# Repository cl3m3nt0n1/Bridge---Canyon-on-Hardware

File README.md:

# Bridge---Canyon-on-Hardware
Welcome to Bridge, the hardware adaptation of Canyon, a convolution reverb plugin. This project utilizes ELK Audio OS and the Raspberry Pi Compute Module 4, featuring three custom-designed boards (1 main board and 2 IO boards). We created this project as the foundation for a complete OpenSource Audio FX Pedal based on community's resources. 

## Overview
Bridge extends Canyon's convolution reverb into the physical realm, combining the power of ELK Audio OS/HifiBerry DAC+ADC and Raspberry Pi Compute Module 4 for a robust audio FX solution.

## Features
- **Convolution Reverb:** Achieve realistic and immersive reverb effects through Canyon.
- **Custom Hardware:** Three boards - 1 main and 2 IO boards - designed for modularity and reusability.
- **ELK Audio OS:** Leverage the efficiency of ELK Audio OS for real-time audio processing.

## Hardware
Bridge comprises the following custom-designed boards:

1. **Main Board:**
   - GPIO/HAT Connector
   - SPI Screen Connector for a [480*320 ILI9488 based screen]([url](https://www.amazon.fr/gp/product/B08NV6SNYH/ref=ppx_yo_dt_b_asin_title_o00_s00?ie=UTF8&psc=1))
   - Raspberry Pi Compute Module 4
   - ATMega328p with ICSP connector for IO management

2. **IO Boards (x2):**
   - Pots and Switches for massive fun
   - Rotary encoder

## Software
Bridge relies on serveral pieces of sotware to run :
1. **ATMega328p:**
  - Potentiometer values conversion
  - Screen management
  - Serial communication with CM4
2. **Compute Module 4:**
  - Running ELK Audio OS for real-time audio processing
  - IO management
  - OSC
  - Serial Communication with ATMega328p

## Contributing
We welcome and encourage contributions to enhance Bridge! If you have ideas, bug fixes, or new features, please open an issue or submit a pull request.

## License
The software contained in this project is licensed under the GPL3 license. The hardware is licensed under the Creative Commons v4.0.

Happy coding with Bridge!

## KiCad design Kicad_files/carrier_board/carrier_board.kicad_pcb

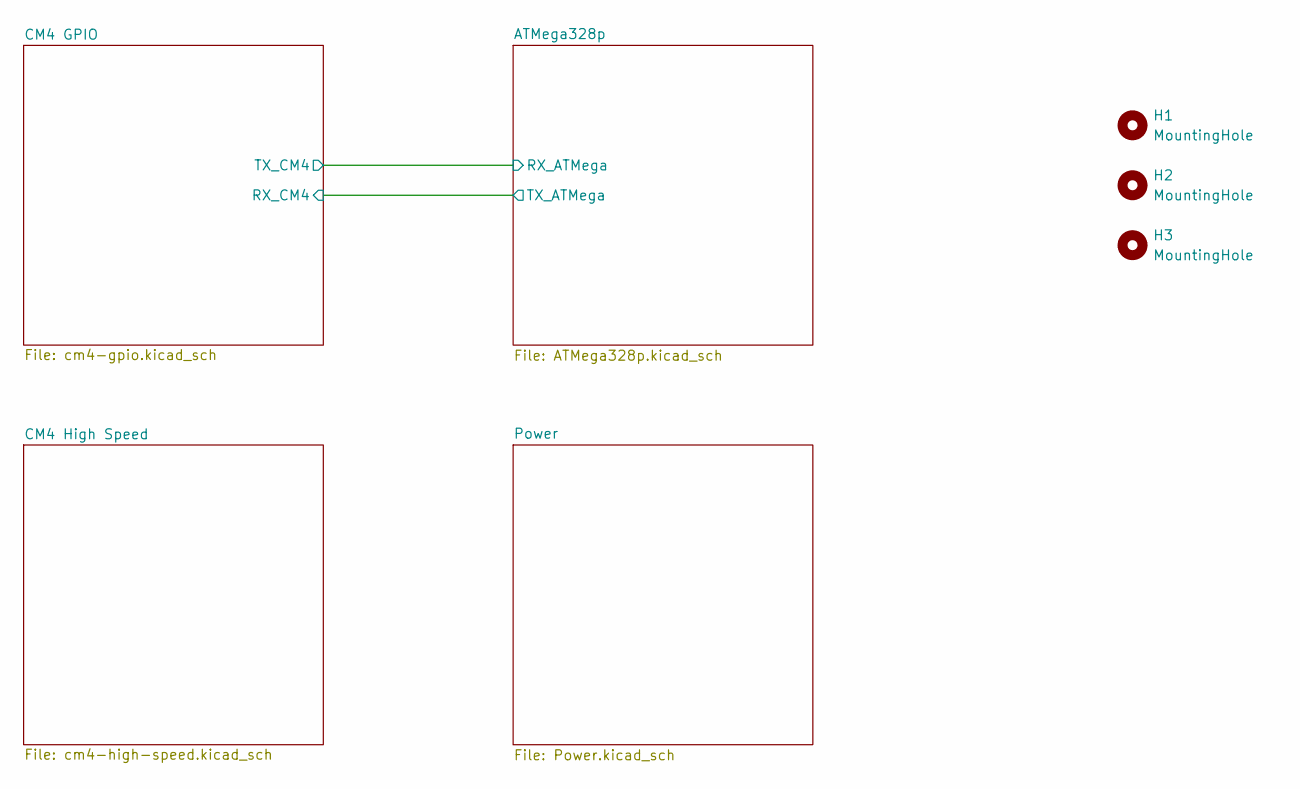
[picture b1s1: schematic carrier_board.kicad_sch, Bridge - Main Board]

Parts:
H1, H2, H3: MountingHole; MountingHole_2.2mm_M2

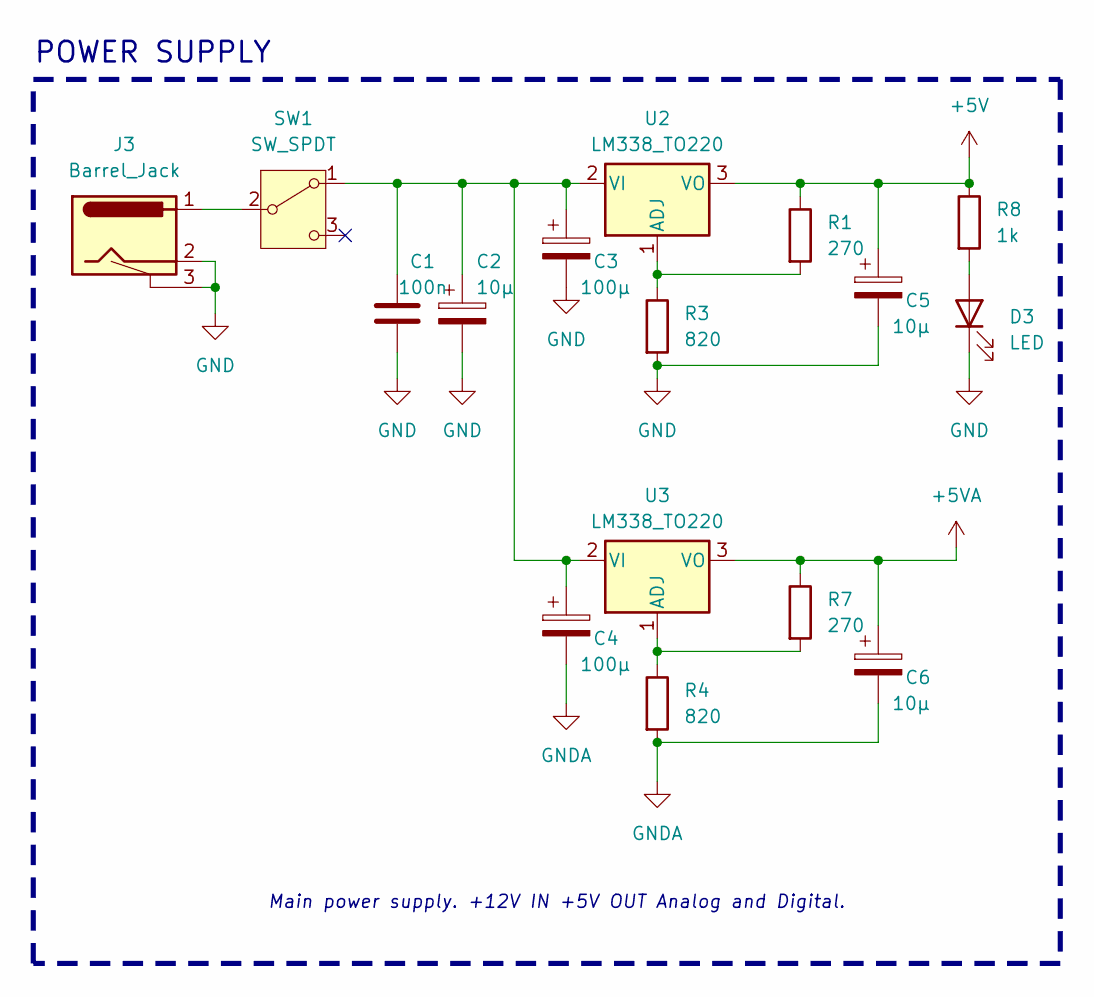
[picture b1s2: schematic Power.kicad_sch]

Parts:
C1: 100n; C_0402_1005Metric
C2, C5, C6: 10µ; CAPMP3216X180N
C3, C4: 100µ; C_1812_4532Metric
D3: LED; LED_D3.0mm
J3: Barrel_Jack; BarrelJack_Horizontal
R1, R7: 270; R_0603_1608Metric
R3, R4: 820; R_0603_1608Metric
R8: 1k; R_0402_1005Metric
SW1: SW_SPDT; SW_Push_1P2T_Vertical_E-Switch_800UDP8P1A1M6
U2, U3: LM338_TO220; TO-220-3_Vertical

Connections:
+5V: C5.1, R1.1, R8.1, U2.3 (VO); also elsewhere on the board
+5VA: C6.1, R7.1, U3.3 (VO); also elsewhere on the board
GND: C1.2, C2.2, C3.2, C5.2, D3.1 (K), J3.2, J3.3, R3.2; also elsewhere on the board
GNDA: C4.2, C6.2, R4.2; also elsewhere on the board
unnamed: D3.2 (A), R8.2
unnamed: C1.1, C2.1, C3.1, C4.1, SW1.1 (A), U2.2 (VI), U3.2 (VI)
unnamed: J3.1, SW1.2 (B)
unnamed: R1.2, R3.1, U2.1 (ADJ)
unnamed: R4.1, R7.2, U3.1 (ADJ)

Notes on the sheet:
POWER SUPPLY
Main power supply. +12V IN +5V OUT Analog and Digital.

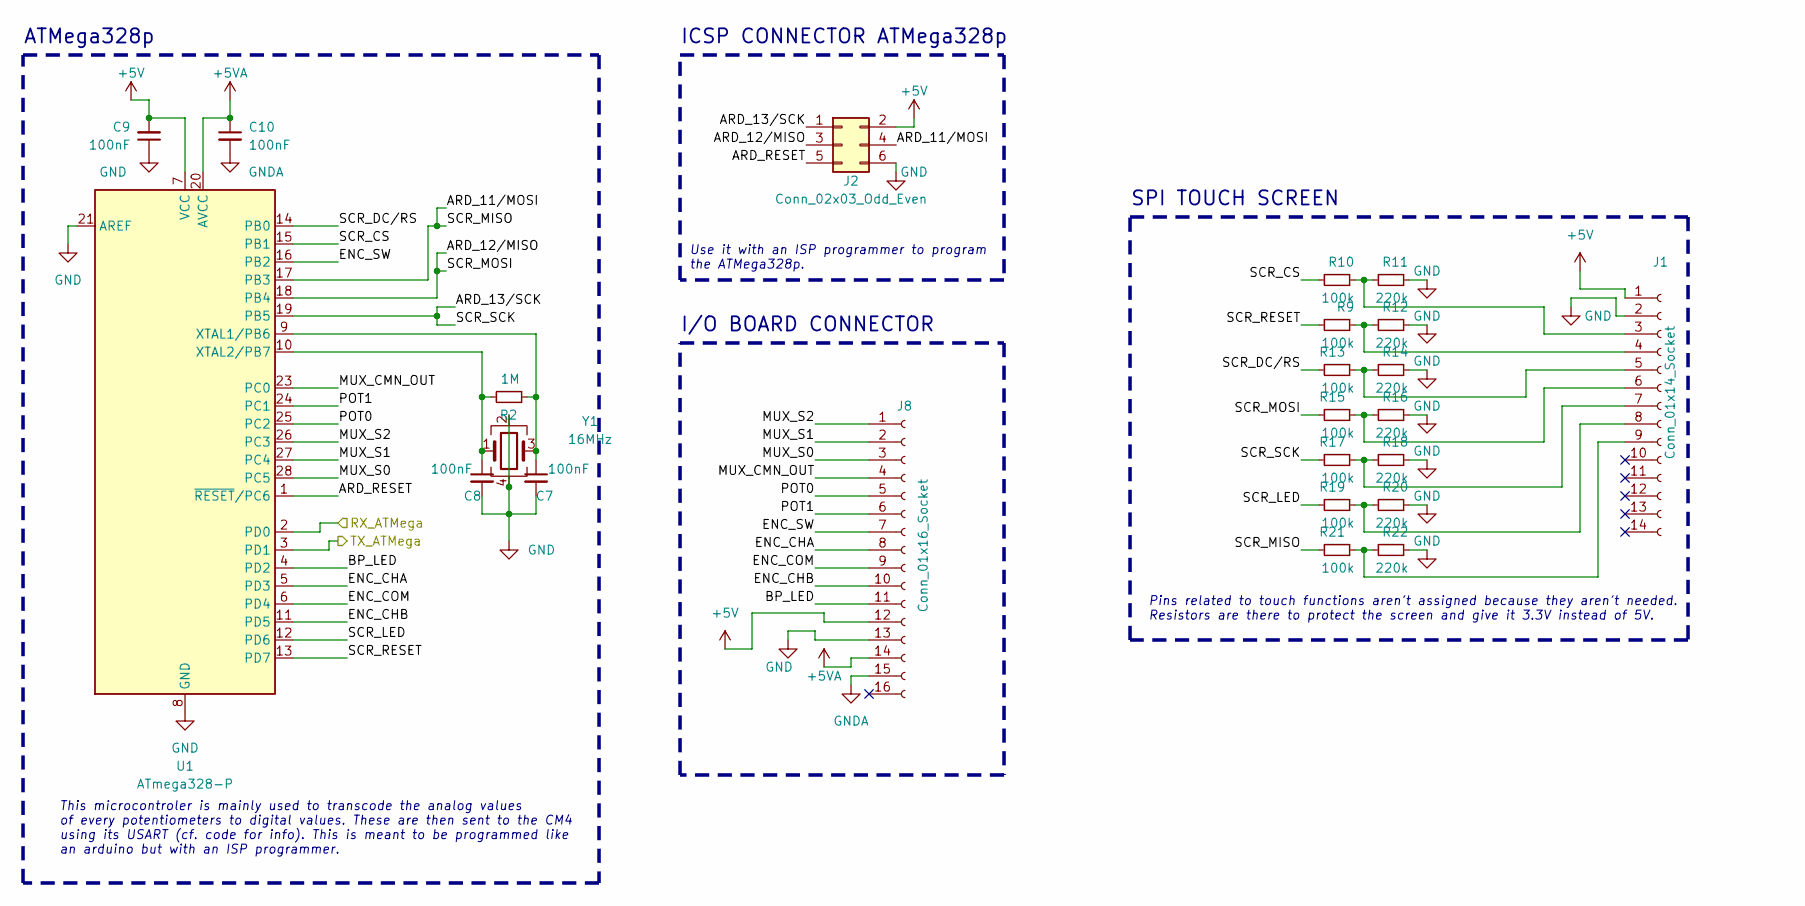
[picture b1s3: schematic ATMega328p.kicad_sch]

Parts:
C7, C8, C9, C10: 100nF; C_0402_1005Metric
J1: Conn_01x14_Socket; PinSocket_1x14_P2.54mm_Vertical
J2: Conn_02x03_Odd_Even; PinHeader_2x03_P2.00mm_Vertical
J8: Conn_01x16_Socket; Hirose_FH12-16S-0.5SH_1x16-1MP_P0.50mm_Horizontal
R2: 1M; R_0402_1005Metric
R9, R10, R13, R15, R17, R19, R21: 100k; R_0402_1005Metric
R11, R12, R14, R16, R18, R20, R22: 220k; R_0603_1608Metric
U1: ATmega328-P; DIP-28_W7.62mm
Y1: 16MHz; Crystal_SMD_3225-4Pin_3.2x2.5mm

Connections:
+5V: C9.2, J1.1, J2.2, J8.12, U1.7 (VCC); also elsewhere on the board
+5VA: C10.1, J8.14, U1.20 (AVCC); also elsewhere on the board
/ATMega328p/ARD_11/MOSI: J2.4, R21.1, U1.17 (PB3)
/ATMega328p/ARD_12/MISO: J2.3, R15.1, U1.18 (PB4)
/ATMega328p/ARD_13/SCK: J2.1, R17.1, U1.19 (PB5)
/ATMega328p/ARD_RESET: J2.5, U1.1 (~RESET/PC6)
/ATMega328p/BP_LED: J8.11, U1.4 (PD2)
/ATMega328p/ENC_CHA: J8.8, U1.5 (PD3)
/ATMega328p/ENC_CHB: J8.10, U1.11 (PD5)
/ATMega328p/ENC_COM: J8.9, U1.6 (PD4)
/ATMega328p/ENC_SW: J8.7, U1.16 (PB2)
/ATMega328p/MUX_CMN_OUT: J8.4, U1.23 (PC0)
/ATMega328p/MUX_S0: J8.3, U1.28 (PC5)
/ATMega328p/MUX_S1: J8.2, U1.27 (PC4)
/ATMega328p/MUX_S2: J8.1, U1.26 (PC3)
/ATMega328p/POT0: J8.5, U1.25 (PC2)
/ATMega328p/POT1: J8.6, U1.24 (PC1)
/ATMega328p/SCR_CS: R10.1, U1.15 (PB1)
/ATMega328p/SCR_DC/RS: R13.1, U1.14 (PB0)
/ATMega328p/SCR_LED: R19.1, U1.12 (PD6)
/ATMega328p/SCR_RESET: R9.1, U1.13 (PD7)
/CM4 GPIO/GPIO14: U1.2 (PD0); also elsewhere on the board
/CM4 GPIO/GPIO15: U1.3 (PD1); also elsewhere on the board
GND: C7.2, C8.2, C9.1, J1.2, J2.6, J8.13, R11.2, R12.2, R14.2, R16.2, R18.2, R20.2, R22.2, U1.8 (GND), U1.21 (AREF), U1.22 (GND), Y1.2, Y1.4; also elsewhere on the board
GNDA: C10.2, J8.15; also elsewhere on the board
unnamed: J1.3, R10.2, R11.1
unnamed: J1.4, R9.2, R12.1
unnamed: J1.5, R13.2, R14.1
unnamed: J1.6, R15.2, R16.1
unnamed: J1.7, R17.2, R18.1
unnamed: J1.8, R19.2, R20.1
unnamed: J1.9, R21.2, R22.1
unnamed: C7.1, R2.1, U1.9 (XTAL1/PB6), Y1.3
unnamed: C8.1, R2.2, U1.10 (XTAL2/PB7), Y1.1

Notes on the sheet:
I/O BOARD CONNECTOR
This microcontroler is mainly used to transcode the analog values of every potentiometers to digital values. These are then sent to the CM4 using its USART (cf. code for info). This is meant to be programmed like an arduino but with an ISP programmer.
Use it with an ISP programmer to program the ATMega328p.
SPI TOUCH SCREEN
ICSP CONNECTOR ATMega328p
ATMega328p
Pins related to touch functions aren't assigned because they aren't needed. Resistors are there to protect the screen and give it 3.3V instead of 5V.

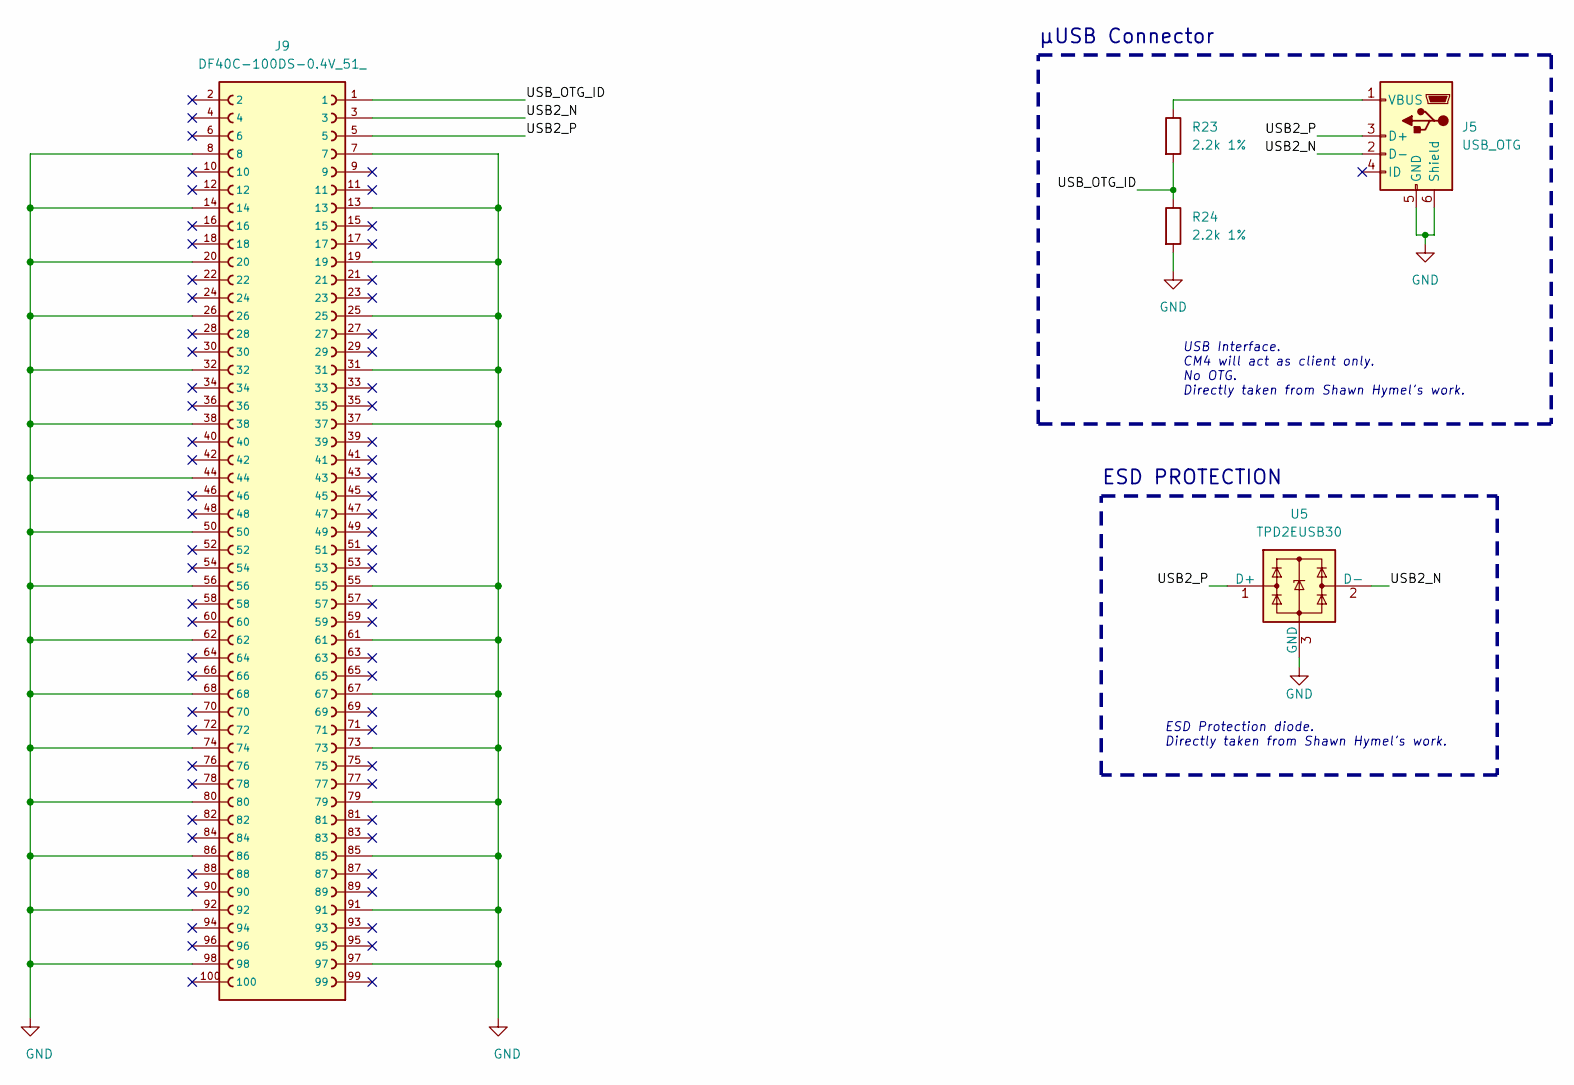
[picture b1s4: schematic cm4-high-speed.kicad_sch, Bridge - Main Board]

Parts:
J5: USB_OTG; USB_Micro-B_EDAC_UCON00686
J9: DF40C-100DS-0.4V_51_; HIROSE_DF40C-100DS-0.4V_51_; PARTREV Oct.1.2023
R23, R24: 2.2k 1%; R_0402_1005Metric
U5: TPD2EUSB30; Texas_DRT-3

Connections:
/CM4 High Speed/USB2_N: J5.2 (D-), J9.3, U5.2 (D-)
/CM4 High Speed/USB2_P: J5.3 (D+), J9.5, U5.1 (D+)
/CM4 High Speed/USB_OTG_ID: J9.1, R23.2, R24.1
GND: J5.5 (GND), J5.6 (Shield), J9.7, J9.8, J9.13, J9.14, J9.19, J9.20, J9.25, J9.26, J9.31, J9.32, J9.37, J9.38, J9.44, J9.50, J9.55, J9.56, J9.61, J9.62, J9.67, J9.68, J9.73, J9.74, J9.79, J9.80, J9.85, J9.86, J9.91, J9.92, J9.97, J9.98, R24.2, U5.3 (GND); also elsewhere on the board
unnamed: J5.1 (VBUS), R23.1

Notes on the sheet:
µUSB Connector
ESD PROTECTION
USB Interface. CM4 will act as client only. No OTG. Directly taken from Shawn Hymel's work.
ESD Protection diode. Directly taken from Shawn Hymel's work.

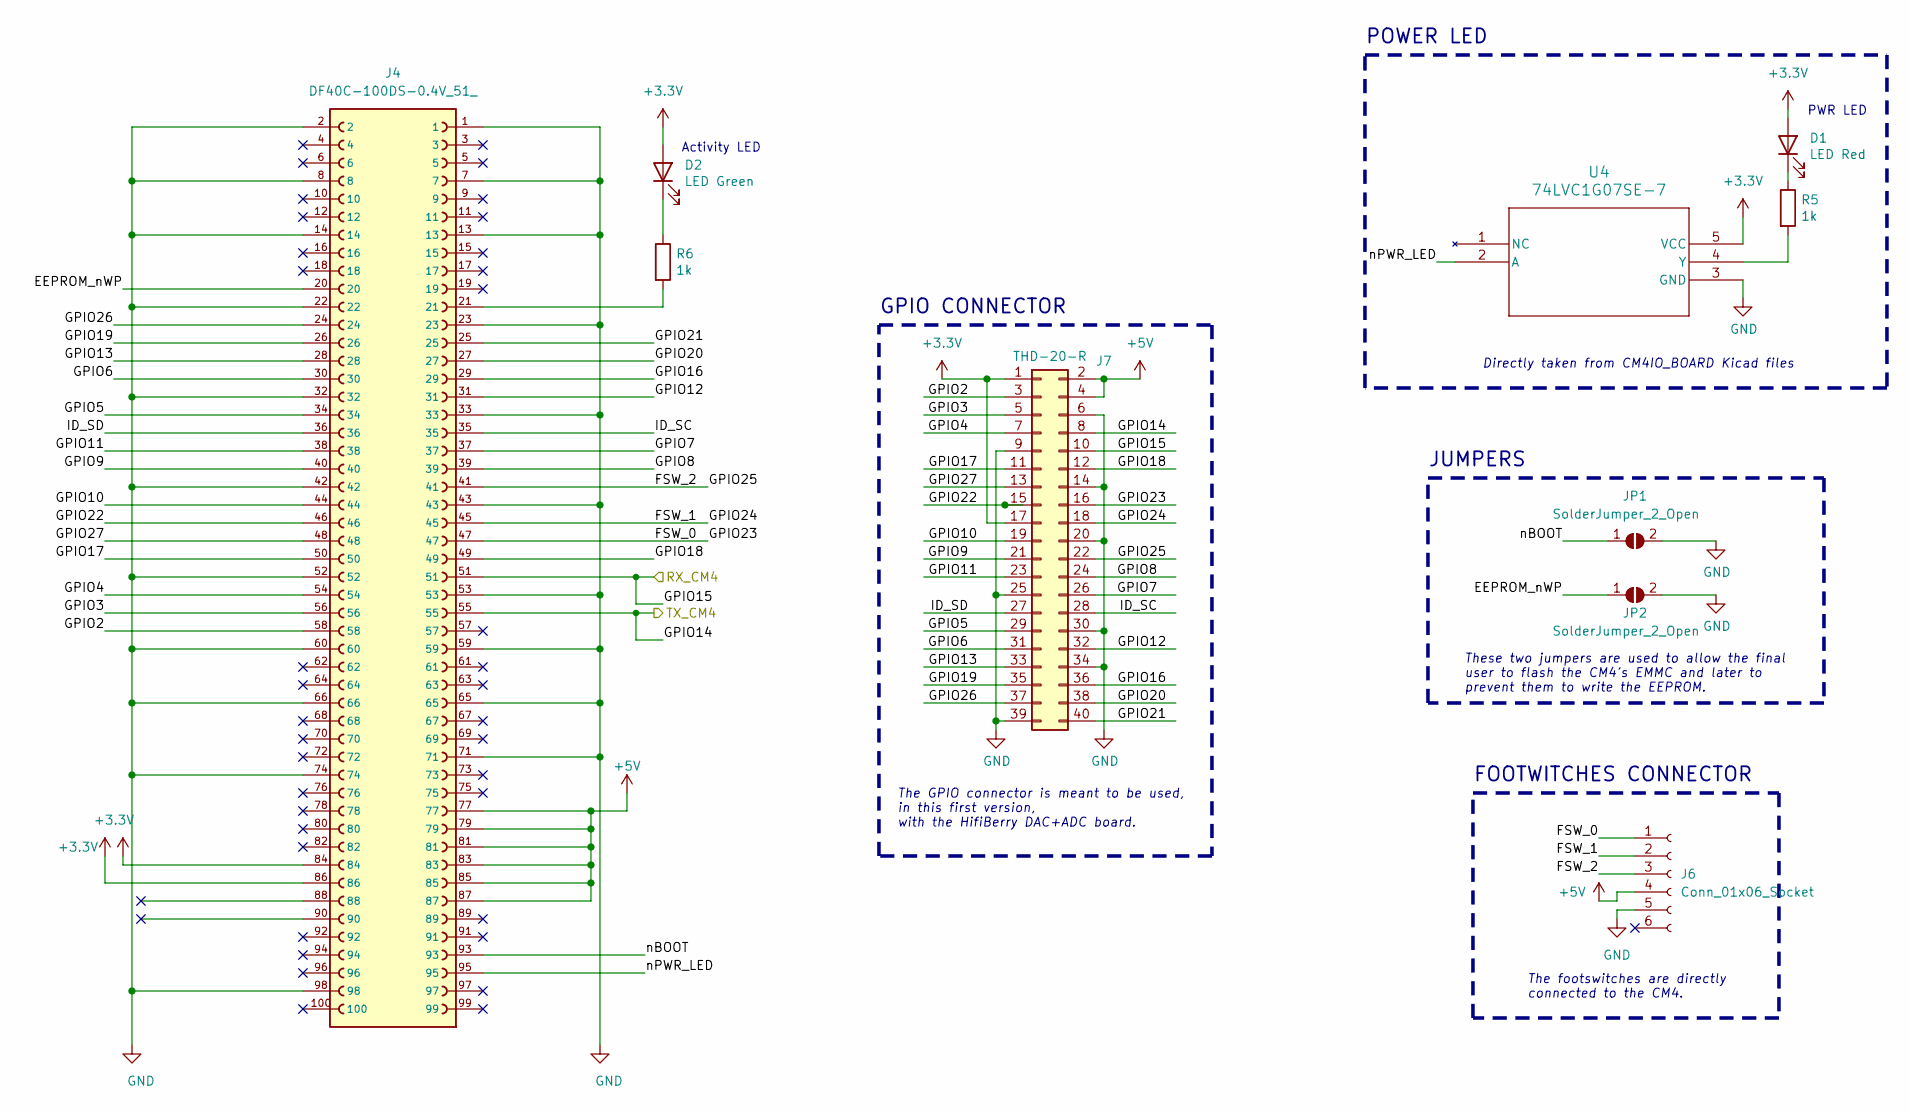
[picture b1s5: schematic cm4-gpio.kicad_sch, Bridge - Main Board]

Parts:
D1: LED Red; LED_0603_1608Metric; Part Description Red 620nm LED Indication - Discrete 2.2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
D2: LED Green; LED_0603_1608Metric; Part Description Green 572nm LED Indication - Discrete 2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
J4: DF40C-100DS-0.4V_51_; HIROSE_DF40C-100DS-0.4V_51_; PARTREV Oct.1.2023
J6: Conn_01x06_Socket; Hirose_FH12-6S-0.5SH_1x06-1MP_P0.50mm_Horizontal
J7: THD-20-R; PinHeader_2x20_P2.54mm_Vertical; Part Description PinHeader_2x20_P2.54mm_Vertical
JP1, JP2: SolderJumper_2_Open; PinHeader_1x02_P2.00mm_Vertical
R5, R6: 1k; R_0402_1005Metric; Part Description Resistor 1K M1005 1% 63mW
U4: 74LVC1G07SE-7; SOT353_DIO

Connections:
+3.3V: D1.2 (A), D2.2 (A), J4.84, J4.86, J7.1, J7.17, U4.5 (VCC)
+5V: J4.77, J4.79, J4.81, J4.83, J4.85, J4.87, J6.4, J7.2, J7.4; also elsewhere on the board
/CM4 GPIO/EEPROM_nWP: J4.20, JP2.1 (A)
/CM4 GPIO/FSW_0: J4.47, J6.1, J7.16
/CM4 GPIO/FSW_1: J4.45, J6.2, J7.18
/CM4 GPIO/FSW_2: J4.41, J6.3, J7.22
/CM4 GPIO/GPIO2: J4.58, J7.3
/CM4 GPIO/GPIO3: J4.56, J7.5
/CM4 GPIO/GPIO4: J4.54, J7.7
/CM4 GPIO/GPIO5: J4.34, J7.29
/CM4 GPIO/GPIO6: J4.30, J7.31
/CM4 GPIO/GPIO7: J4.37, J7.26
/CM4 GPIO/GPIO8: J4.39, J7.24
/CM4 GPIO/GPIO9: J4.40, J7.21
/CM4 GPIO/GPIO10: J4.44, J7.19
/CM4 GPIO/GPIO11: J4.38, J7.23
/CM4 GPIO/GPIO12: J4.31, J7.32
/CM4 GPIO/GPIO13: J4.28, J7.33
/CM4 GPIO/GPIO14: J4.55, J7.8; also elsewhere on the board
/CM4 GPIO/GPIO15: J4.51, J7.10; also elsewhere on the board
/CM4 GPIO/GPIO16: J4.29, J7.36
/CM4 GPIO/GPIO17: J4.50, J7.11
/CM4 GPIO/GPIO18: J4.49, J7.12
/CM4 GPIO/GPIO19: J4.26, J7.35
/CM4 GPIO/GPIO20: J4.27, J7.38
/CM4 GPIO/GPIO21: J4.25, J7.40
/CM4 GPIO/GPIO22: J4.46, J7.15
/CM4 GPIO/GPIO26: J4.24, J7.37
/CM4 GPIO/GPIO27: J4.48, J7.13
/CM4 GPIO/ID_SC: J4.35, J7.28
/CM4 GPIO/ID_SD: J4.36, J7.27
/CM4 GPIO/nBOOT: J4.93, JP1.1 (A)
/CM4 GPIO/nPWR_LED: J4.95, U4.2 (A)
GND: J4.1, J4.2, J4.7, J4.8, J4.13, J4.14, J4.22, J4.23, J4.32, J4.33, J4.42, J4.43, J4.52, J4.53, J4.59, J4.60, J4.65, J4.66, J4.71, J4.74, J4.98, J6.5, J7.6, J7.9, J7.14, J7.20, J7.25, J7.30, J7.34, J7.39, JP1.2 (B), JP2.2 (B), U4.3 (GND); also elsewhere on the board
unnamed: D1.1 (K), R5.1
unnamed: D2.1 (K), R6.1
unnamed: J4.21, R6.2
unnamed: R5.2, U4.4 (Y)

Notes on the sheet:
The footswitches are directly connected to the CM4.
FOOTWITCHES CONNECTOR
JUMPERS
POWER LED
PWR LED
Activity LED
These two jumpers are used to allow the final user to flash the CM4's EMMC and later to prevent them to write the EEPROM.
The GPIO connector is meant to be used, in this first version, with the HifiBerry DAC+ADC board.
GPIO CONNECTOR
Directly taken from CM4IO_BOARD Kicad files

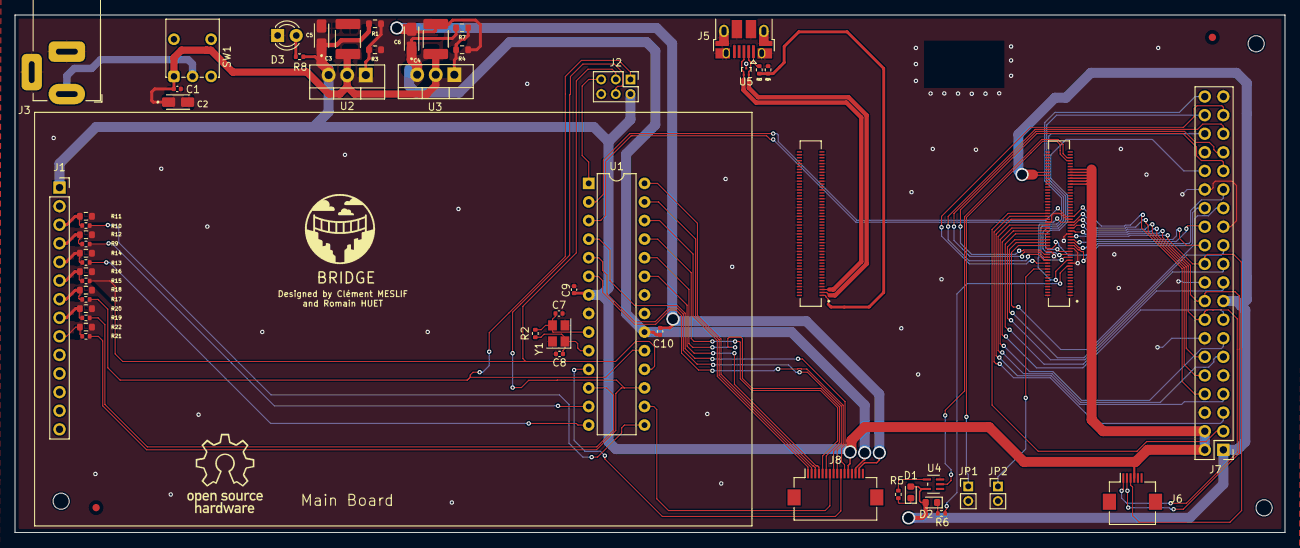
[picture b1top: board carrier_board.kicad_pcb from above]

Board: 4 copper layers, 173.5 x 70.7 mm, 58 parts (0 on the bottom side), 77 nets.

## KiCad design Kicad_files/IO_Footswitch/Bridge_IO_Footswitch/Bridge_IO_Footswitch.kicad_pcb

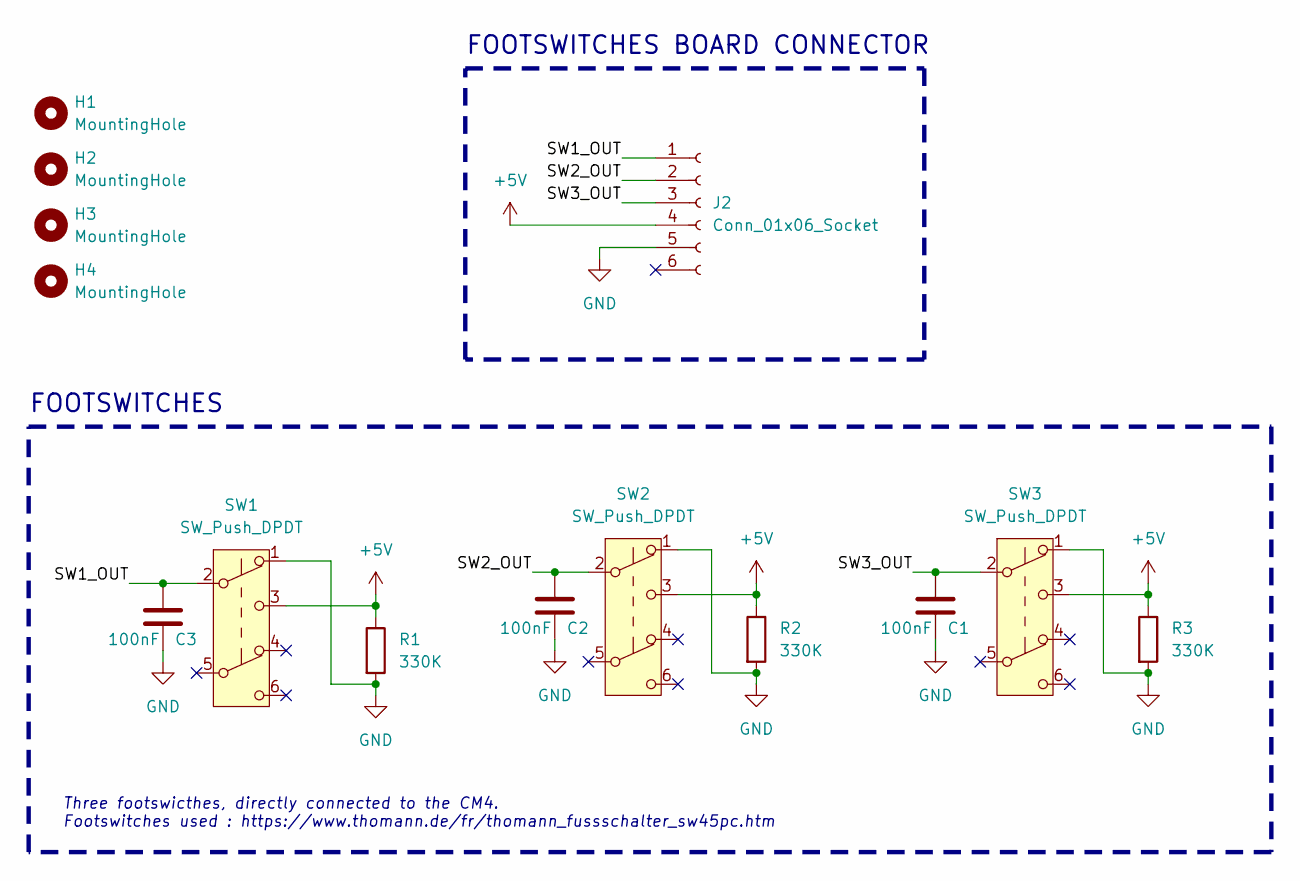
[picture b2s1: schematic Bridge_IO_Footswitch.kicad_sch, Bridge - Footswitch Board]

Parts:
C1, C2, C3: 100nF; C_0402_1005Metric
H1, H2, H3, H4: MountingHole; MountingHole_2.2mm_M2
J2: Conn_01x06_Socket; Hirose_FH12-6S-0.5SH_1x06-1MP_P0.50mm_Horizontal
R1, R2, R3: 330K; R_0603_1608Metric
SW1, SW2, SW3: SW_Push_DPDT; Switch 2 DPDT

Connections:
+5V: J2.4, R1.1, R2.1, R3.1, SW1.3 (C), SW2.3 (C), SW3.3 (C)
/SW1_OUT: C3.1, J2.1, SW1.2 (B)
/SW2_OUT: C2.1, J2.2, SW2.2 (B)
/SW3_OUT: C1.1, J2.3, SW3.2 (B)
GND: C1.2, C2.2, C3.2, J2.5, R1.2, R2.2, R3.2, SW1.1 (A), SW2.1 (A), SW3.1 (A)

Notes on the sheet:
FOOTSWITCHES BOARD CONNECTOR
Three footswicthes, directly connected to the CM4. Footswitches used : https://www.thomann.de/fr/thomann_fussschalter_sw45pc.htm
FOOTSWITCHES

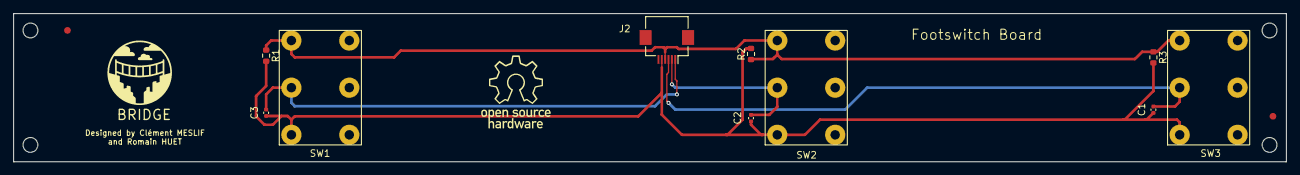
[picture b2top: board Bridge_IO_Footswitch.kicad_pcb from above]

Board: 4 copper layers, 189.0 x 22.0 mm, 14 parts (0 on the bottom side), 5 nets.

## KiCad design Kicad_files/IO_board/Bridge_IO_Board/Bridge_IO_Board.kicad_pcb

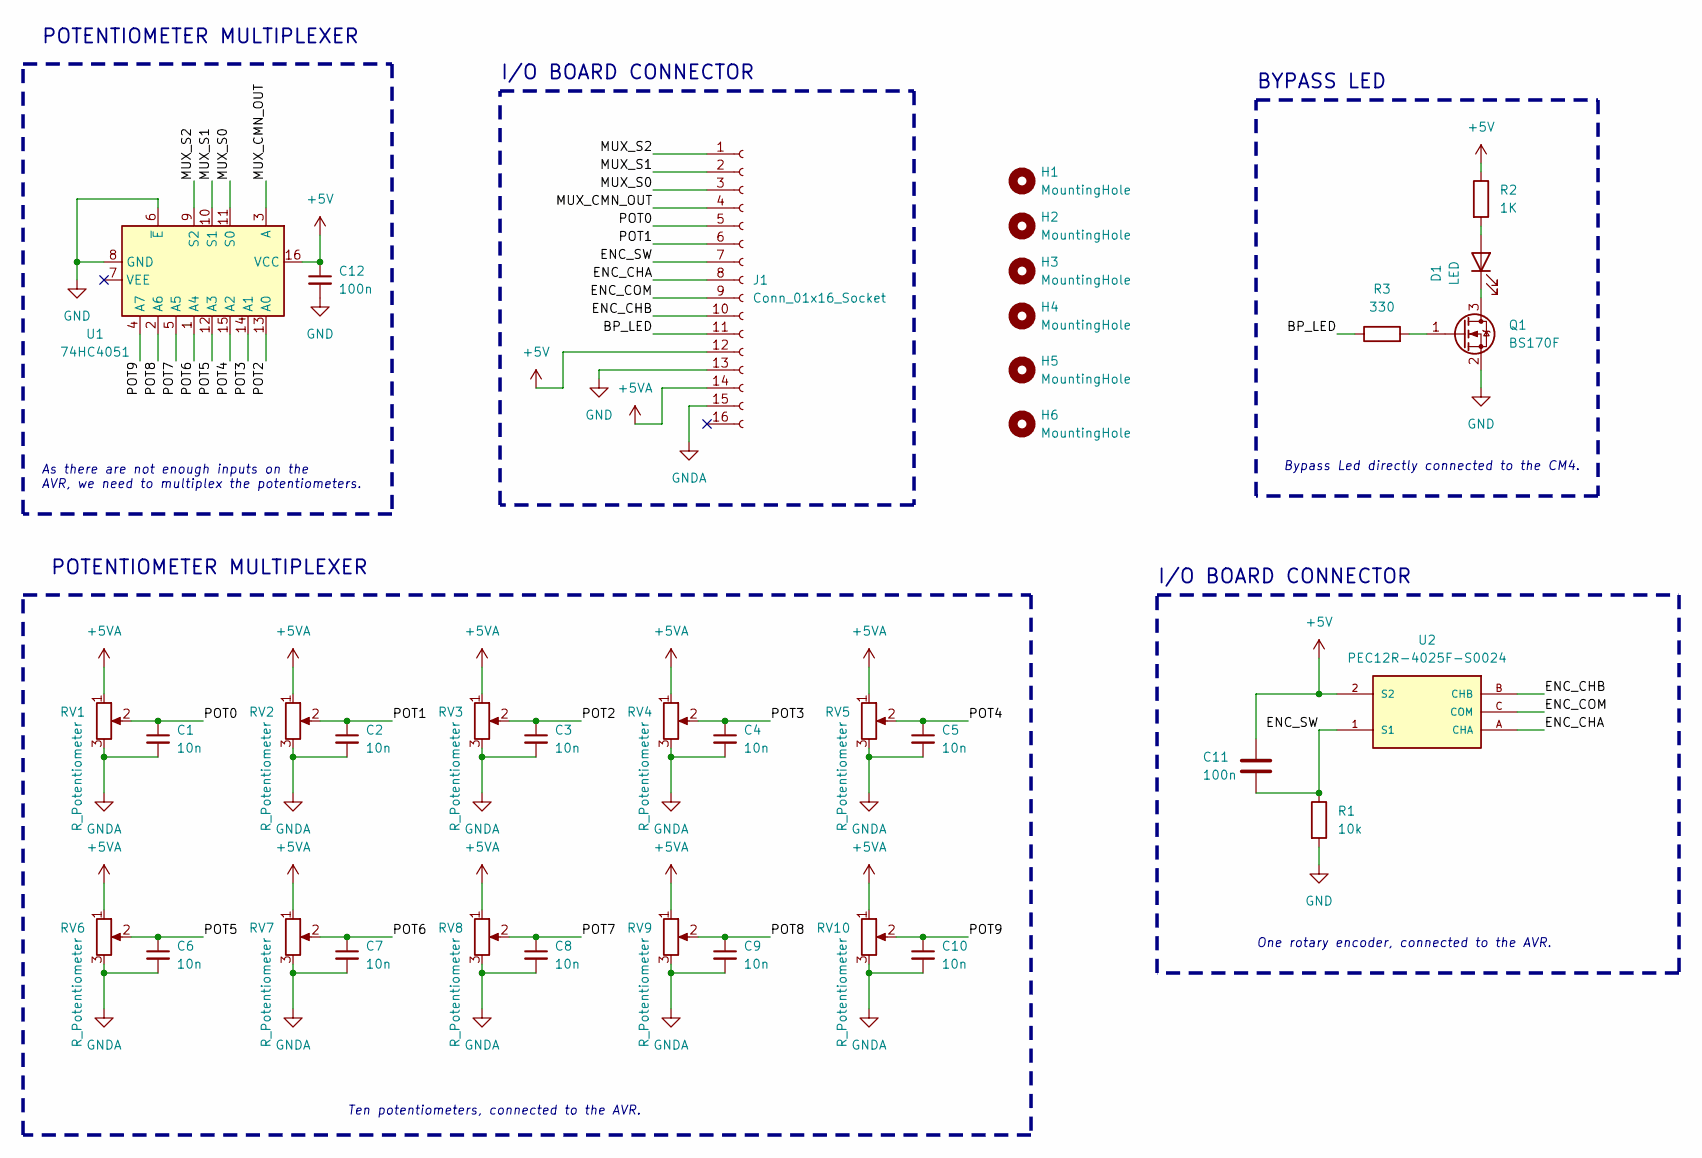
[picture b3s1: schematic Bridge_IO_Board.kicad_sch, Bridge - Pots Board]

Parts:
C1, C2, C3, C4, C5, C6, C7, C8, C9, C10: 10n; C_0402_1005Metric
C11, C12: 100n; C_0402_1005Metric
D1: LED; LED_D5.0mm
H1, H2, H3, H4, H5, H6: MountingHole; MountingHole_2.2mm_M2
J1: Conn_01x16_Socket; Hirose_FH12-16S-0.5SH_1x16-1MP_P0.50mm_Horizontal
Q1: BS170F; SOT-23
R1: 10k; R_0402_1005Metric
R2: 1K; R_0402_1005Metric
R3: 330; R_0402_1005Metric
RV1, RV2, RV3, RV4, RV5, RV6, RV7, RV8, RV9, RV10: R_Potentiometer; TRIM_R0904NB10KL-25KQ
U1: 74HC4051; DIP-16_W10.16mm_LongPads
U2: PEC12R-4025F-S0024; ENC_PEC12R-4025F-S0024

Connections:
+5V: C11.1, C12.1, J1.12, R2.1, U1.16 (VCC), U2.2 (S2)
+5VA: J1.14, RV1.1, RV2.1, RV3.1, RV4.1, RV5.1, RV6.1, RV7.1, RV8.1, RV9.1, RV10.1
/BP_LED: J1.11, R3.1
/ENC_CHA: J1.8, U2.A (CHA)
/ENC_CHB: J1.10, U2.B (CHB)
/ENC_COM: J1.9, U2.C (COM)
/ENC_SW: C11.2, J1.7, R1.1, U2.1 (S1)
/MUX_CMN_OUT: J1.4, U1.3 (A)
/MUX_S0: J1.3, U1.11 (S0)
/MUX_S1: J1.2, U1.10 (S1)
/MUX_S2: J1.1, U1.9 (S2)
/POT0: C1.1, J1.5, RV1.2
/POT1: C2.1, J1.6, RV2.2
/POT2: C3.1, RV3.2, U1.13 (A0)
/POT3: C4.1, RV4.2, U1.14 (A1)
/POT4: C5.1, RV5.2, U1.15 (A2)
/POT5: C6.1, RV6.2, U1.12 (A3)
/POT6: C7.1, RV7.2, U1.1 (A4)
/POT7: C8.1, RV8.2, U1.5 (A5)
/POT8: C9.1, RV9.2, U1.2 (A6)
/POT9: C10.1, RV10.2, U1.4 (A7)
GND: C12.2, J1.13, Q1.2 (S), R1.2, U1.6 (~E), U1.8 (GND)
GNDA: C1.2, C2.2, C3.2, C4.2, C5.2, C6.2, C7.2, C8.2, C9.2, C10.2, J1.15, RV1.3, RV2.3, RV3.3, RV4.3, RV5.3, RV6.3, RV7.3, RV8.3, RV9.3, RV10.3
unnamed: D1.2 (A), R2.2
unnamed: D1.1 (K), Q1.3 (D)
unnamed: Q1.1 (G), R3.2

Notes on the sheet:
One rotary encoder, connected to the AVR.
POTENTIOMETER MULTIPLEXER
As there are not enough inputs on the AVR, we need to multiplex the potentiometers.
BYPASS LED
Ten potentiometers, connected to the AVR.
Bypass Led directly connected to the CM4.
I/O BOARD CONNECTOR

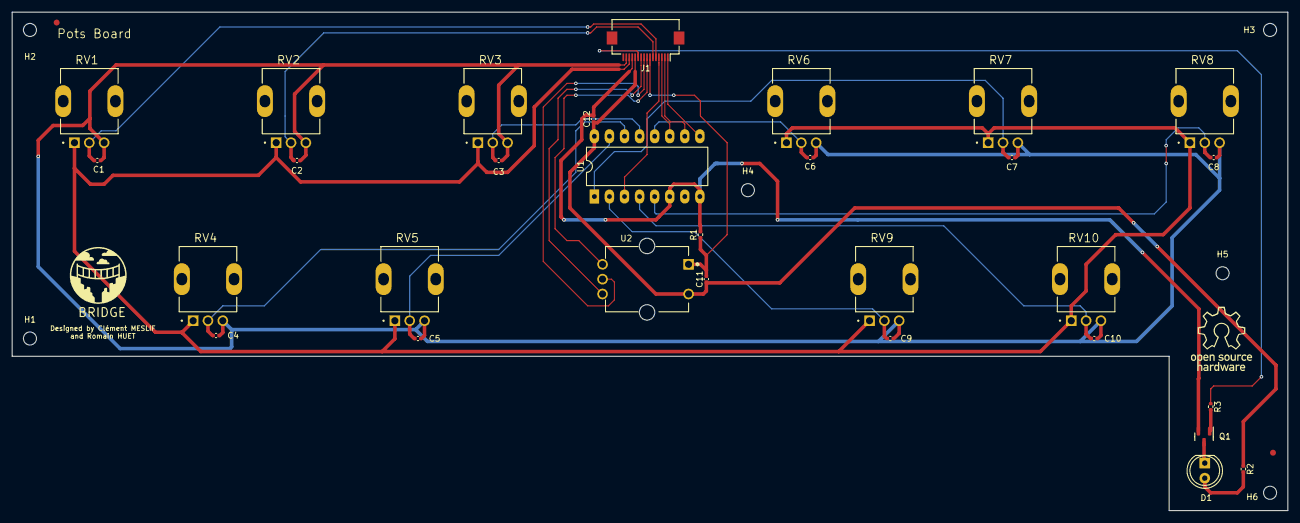
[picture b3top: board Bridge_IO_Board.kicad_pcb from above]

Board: 4 copper layers, 215.0 x 84.0 mm, 36 parts (0 on the bottom side), 26 nets.

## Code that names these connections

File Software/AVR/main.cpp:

/*
 * Authors : @Cl3m3nt0n1 - @RomainH27
 * Licence : GPL3
 */
#include <Arduino.h>

// Define addresses for each potentiometer
#define POT1_ADDR 1
#define POT2_ADDR 2
#define POT3_ADDR 3
#define POT4_ADDR 4
#define POT5_ADDR 5
#define POT6_ADDR 6
const char* specialString = "READY?";


// Variables to store potentiometer values
int pot1Val = 0;
int pot2Val = 0;
int pot3Val = 0;
int pot4Val = 0;
int pot5Val = 0;
int pot6Val = 0;

// Analog pin assignments for each potentiometer
unsigned char pot1 = A0;
unsigned char pot2 = A1;
unsigned char pot3 = A2;
unsigned char pot4 = A3;
unsigned char pot5 = A4;
unsigned char pot6 = A5;


/**
 * @brief Prepares a string representation of a potentiometer value.
 *
 * This function takes the analog pin address of a potentiometer, reads its
 * value, and creates a formatted string to represent the address and value.
 *
 * @param potAddr The analog pin address of the potentiometer.
 * @return A formatted string containing the address and value.
 */
String preparePot(unsigned char potAddr)
{
    String stringToPrint = "@";
    switch (potAddr)
    {
    case A0:
        stringToPrint += POT1_ADDR;
        stringToPrint += "/";
        stringToPrint += pot1Val;
        return stringToPrint;
        break;

    case A1:
        stringToPrint += POT2_ADDR;
        stringToPrint += "/";
        stringToPrint += pot2Val;
        return stringToPrint;
        break;

    case A2:
        stringToPrint += POT3_ADDR;
        stringToPrint += "/";
        stringToPrint += pot3Val;
        return stringToPrint;
        break;

    case A3:
        stringToPrint += POT4_ADDR;
        stringToPrint += "/";
        stringToPrint += pot4Val;
        return stringToPrint;
        break;

    case A4:
        stringToPrint += POT5_ADDR;
        stringToPrint += "/";
        stringToPrint += pot5Val;
        return stringToPrint;
        break;

    case A5:
        stringToPrint += POT6_ADDR;
        stringToPrint += "/";
        stringToPrint += pot6Val;
        return stringToPrint;
        break;

    default:
        return "";
        break;
    }
}

/**
 * @brief Initializes the timer for periodic interrupt handling.
 *
 * This function configures Timer1 with a prescaler and initial counter value
 * to generate periodic interrupts for handling potentiometer readings.
 * Period = 10ms
 */
void initTimer()
{
    TCCR1A = 0;          // Init Timer1A
    TCCR1B = 0;          // Init Timer1B
    TCCR1B |= B00000010; // Prescaler = 8
    TCNT1 = 45535;       // Timer Preloading
    TIMSK1 |= B00000001; // Enable Timer Overflow Interrupt
}

/**
 * @brief Handles the timer interrupt to read potentiometer values and send them via UART.
 *
 * This function is called whenever the timer overflows, and it reads the values of all
 * potentiometers and sends them via UART (Serial).
 */
void handleInterrupt()
{
    // Get values from all potentiometers
    pot1Val = analogRead(pot1);
    pot2Val = analogRead(pot2);
    pot3Val = analogRead(pot3);
    pot4Val = analogRead(pot4);
    pot5Val = analogRead(pot5);
    pot6Val = analogRead(pot6);

    // Send data to UART
    Serial.println(preparePot(pot1));
    Serial.println(preparePot(pot2));
    Serial.println(preparePot(pot3));
    Serial.println(preparePot(pot4));
    Serial.println(preparePot(pot5));
    Serial.println(preparePot(pot6));
}

/**
 * @brief Negotiation function.
 *
 * This function wait for inputs on Serial port.
 * If input is 'OK', initiate the communication and
 * begin to send Pots values.
 */
unsigned char negotiate()
{
    if (Serial.available() >  0) { 
    String receivedString = Serial.readStringUntil('\n'); 
    receivedString.trim();
    if (receivedString == specialString) {
      delay(1200);
      Serial.println("OK");
      delay(1000);
      return 1; 
    }
    else
      return 0;
  }
}

/**
 * @brief Setup function called once at the beginning of the program.
 *
 * This function initializes Serial communication, sets up the timer, and enables interrupts.
 */
void setup()
{

    Serial.begin(115200);
    while(!negotiate());
    initTimer();

    // Enable global interrupts
    interrupts();

}

/**
 * @brief Loop function called repeatedly in the main program.
 *
 * This function is intentionally left empty as all operations are handled in the timer interrupt.
 */
void loop() {}

/**
 * @brief Timer1 Overflow Interrupt Service Routine.
 *
 * This function is called whenever Timer1 overflows, triggering the periodic
 * reading and sending of potentiometer values.
 */
ISR(TIMER1_OVF_vect)
{
    TCNT1 = 45535; // Timer Preloading
    // Handle The Timer Overflow Interrupt
    handleInterrupt();
}

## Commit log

2024-02-16 Kicad files
2024-03-04 First part of software

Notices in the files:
Kicad_files/carrier_board/carrier_board.kicad_pcb:
creativecommons.org/licenses/by/4.0
License: CC BY 4.0
